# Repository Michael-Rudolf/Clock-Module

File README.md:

# Clock Module

This is the completely untested clock module for my (now) MRISC-CPU.
Don't use this shit.

## More info
Check README.pdf

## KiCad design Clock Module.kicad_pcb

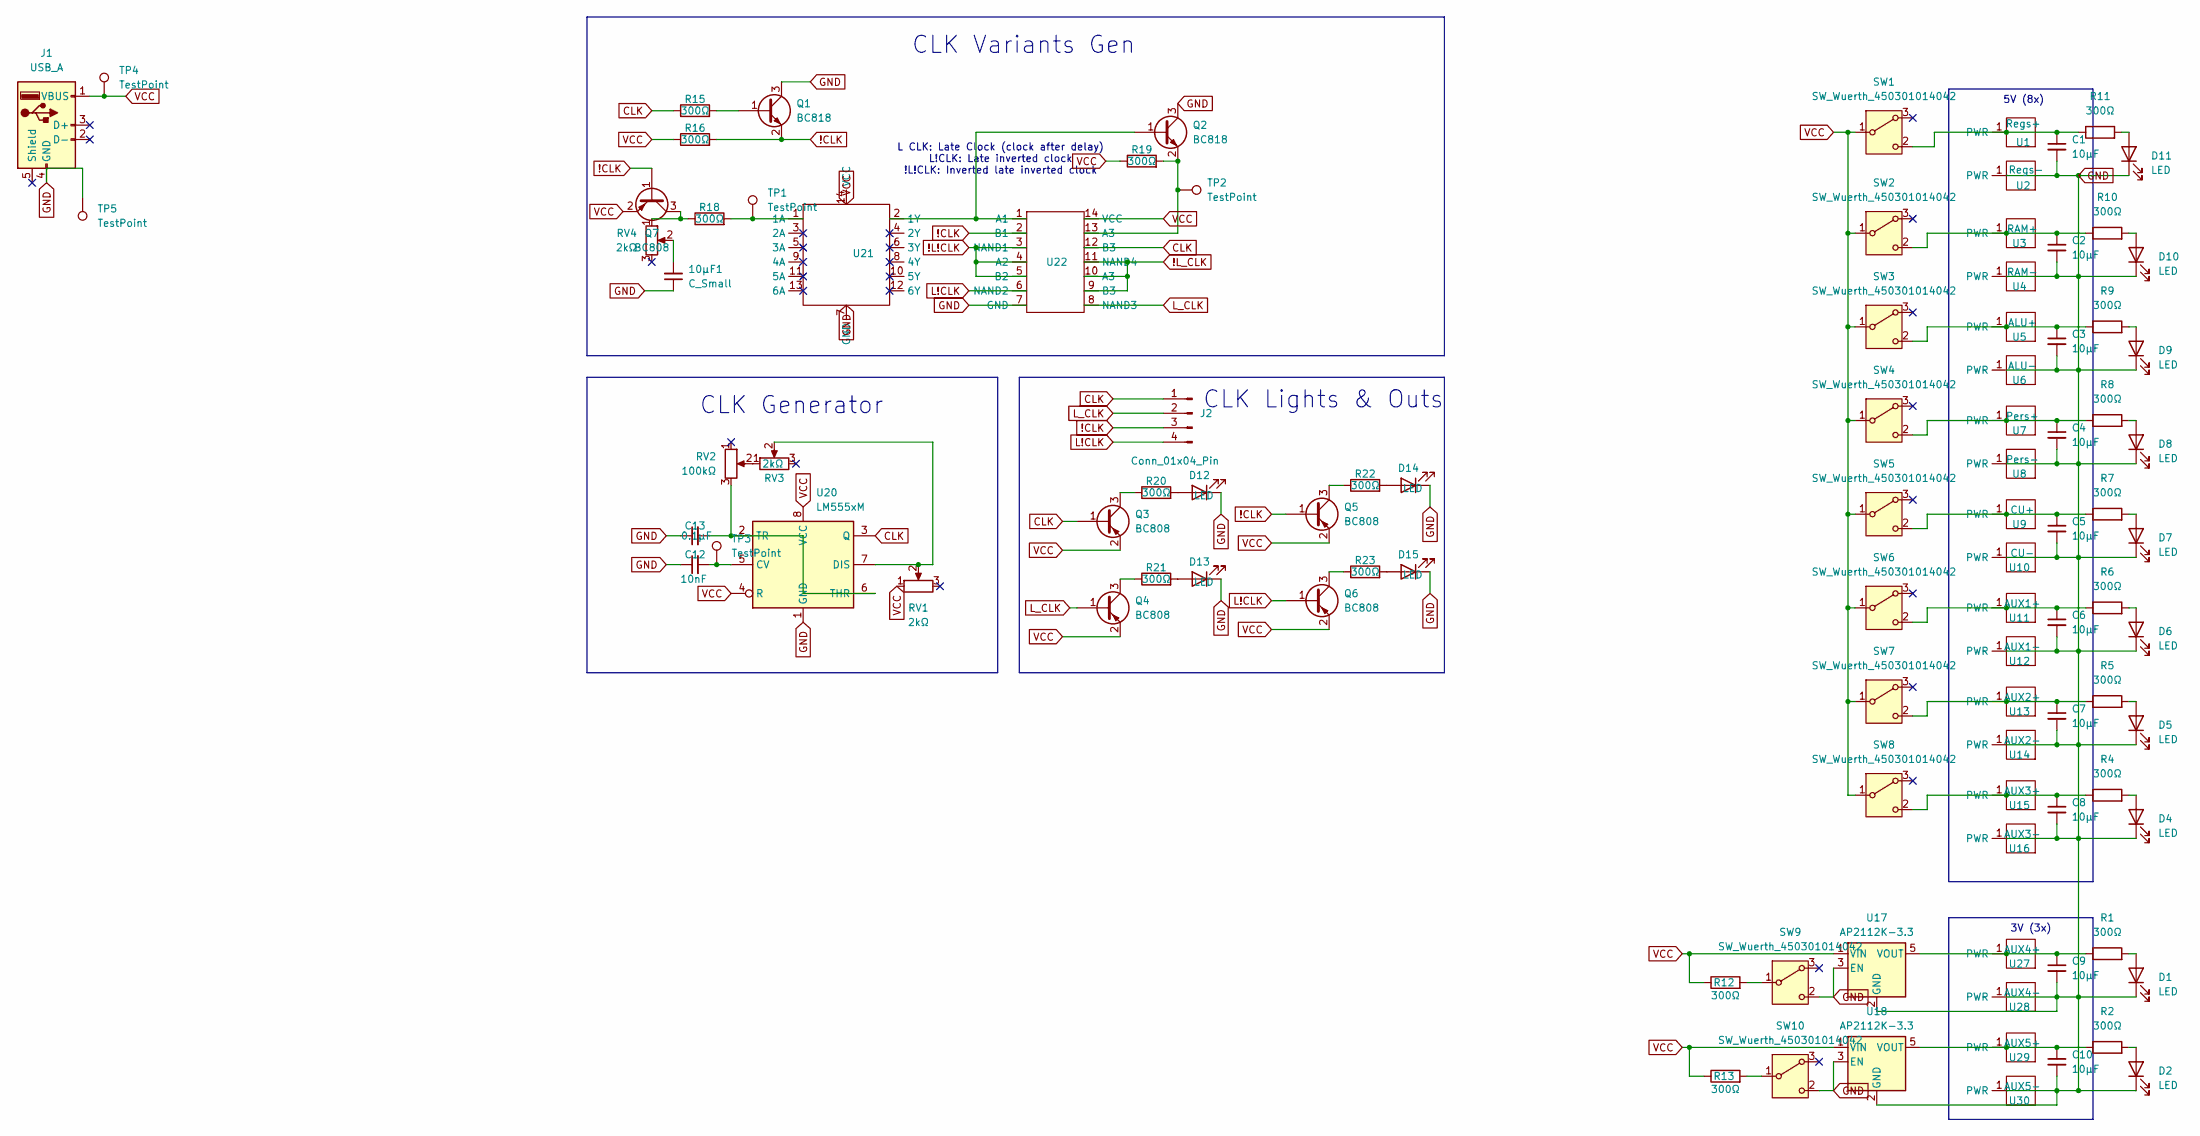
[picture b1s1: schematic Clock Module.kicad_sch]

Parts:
10µF1: C_Small; C_0805_2012Metric_Pad1.18x1.45mm_HandSolder
C1, C2, C3, C4, C5, C6, C7, C8, C9, C10: 10µF; C_0805_2012Metric
C12: 10nF; C_0805_2012Metric_Pad1.18x1.45mm_HandSolder
C13: 0.1µF; C_0805_2012Metric_Pad1.18x1.45mm_HandSolder
D1, D2, D4, D5, D6, D7, D8, D9, D10, D11, D12, D13, D14, D15: LED; LED_0805_2012Metric_Pad1.15x1.40mm_HandSolder
J1: USB_A; USB_A_CONNFLY_DS1095-WNR0
J2: Conn_01x04_Pin; PinHeader_1x04_P2.54mm_Vertical
Q1, Q2: BC818; SOT-23-3
Q3, Q4, Q5, Q6: BC808; SOT-23-3
Q7: BC808; SOT-23
R1, R2, R4, R5, R6, R7, R8, R9, R10, R11, R12, R13, R15, R16, R18, R19, R20, R21, R22, R23: 300Ω; R_0805_2012Metric_Pad1.20x1.40mm_HandSolder
RV1, RV3, RV4: 2kΩ; Potentiometer_Bourns_3299X_Horizontal
RV2: 100kΩ; Potentiometer_Bourns_3299X_Horizontal
SW1, SW2, SW3, SW4, SW5, SW6, SW7, SW8, SW9, SW10: SW_Wuerth_450301014042; SW_Slide-03_Wuerth-WS-SLTV_10x2.5x6.4_P2.54mm
TP1, TP2, TP3, TP4, TP5: TestPoint; TestPoint_Pad_1.0x1.0mm
U1: Regs+; Single Bit Mini Bus
U2: Regs-; Single Bit Mini Bus
U3: RAM+; Single Bit Mini Bus
U4: RAM-; Single Bit Mini Bus
U5: ALU+; Single Bit Mini Bus
U6: ALU-; Single Bit Mini Bus
U7: Pers+; Single Bit Mini Bus
U8: Pers-; Single Bit Mini Bus
U9: CU+; Single Bit Mini Bus
U10: CU-; Single Bit Mini Bus
U11: AUX1+; Single Bit Mini Bus
U12: AUX1-; Single Bit Mini Bus
U13: AUX2+; Single Bit Mini Bus
U14: AUX2-; Single Bit Mini Bus
U15: AUX3+; Single Bit Mini Bus
U16: AUX3-; Single Bit Mini Bus
U17, U18: AP2112K-3.3; SOT-23-5
U20: LM555xM; SOIC-8_3.9x4.9mm_P1.27mm
U21: TSSOP-14_4.4x5mm_P0.65mm
U22: SN74HC03
U27: AUX4+; Single Bit Mini Bus
U28: AUX4-; Single Bit Mini Bus
U29: AUX5+; Single Bit Mini Bus
U30: AUX5-; Single Bit Mini Bus

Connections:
!CLK: J2.3, Q1.2 (E), Q5.1 (B), Q7.1 (B), R16.2, U22.2 (B1)
!L!CLK: U22.3 (NAND1), U22.4 (A2), U22.5 (B2)
!L_CLK: U22.9 (B3), U22.10 (A3), U22.11 (NAND4)
CLK: J2.1, Q3.1 (B), R15.1, U20.3 (Q), U22.12 (B3)
GND: 10µF1.1, C1.2, C2.2, C3.2, C4.2, C5.2, C6.2, C7.2, C8.2, C9.2, C10.2, C12.1, C13.1, D1.1 (K), D2.1 (K), D4.1 (K), D5.1 (K), D6.1 (K), D7.1 (K), D8.1 (K), D9.1 (K), D10.1 (K), D11.1 (K), D12.1 (K), D13.1 (K), D14.1 (K), D15.1 (K), J1.4 (GND), Q1.3 (C), Q2.3 (C), SW9.2 (C), SW10.2 (C), TP5.1, U2.1 (PWR), U4.1 (PWR), U6.1 (PWR), U8.1 (PWR), U10.1 (PWR), U12.1 (PWR), U14.1 (PWR), U16.1 (PWR), U17.2 (GND), U17.3 (EN), U18.2 (GND), U18.3 (EN), U20.1 (GND), U21.7 (GND), U22.7 (GND), U28.1 (PWR), U30.1 (PWR)
L!CLK: J2.4, Q6.1 (B), U22.6 (NAND2)
L_CLK: J2.2, Q4.1 (B), U22.8 (NAND3)
unnamed: 10µF1.2, RV4.2
unnamed: D1.2 (A), R1.2
unnamed: D2.2 (A), R2.2
unnamed: D4.2 (A), R4.2
unnamed: D5.2 (A), R5.2
unnamed: D6.2 (A), R6.2
unnamed: D7.2 (A), R7.2
unnamed: D8.2 (A), R8.2
unnamed: D9.2 (A), R9.2
unnamed: D10.2 (A), R10.2
unnamed: D11.2 (A), R11.2
unnamed: D12.2 (A), R20.2
unnamed: D13.2 (A), R21.2
unnamed: D14.2 (A), R22.2
unnamed: D15.2 (A), R23.2
unnamed: Q1.1 (B), R15.2
unnamed: Q2.1 (B), U21.2 (1Y), U22.1 (A1)
unnamed: Q2.2 (E), R19.2, TP2.1, U22.13 (A3)
unnamed: Q3.3 (C), R20.1
unnamed: Q4.3 (C), R21.1
unnamed: Q5.3 (C), R22.1
unnamed: Q6.3 (C), R23.1
unnamed: Q7.3 (C), R18.1, RV4.1
unnamed: RV2.2, RV3.1
unnamed: C1.1, R11.1, SW1.2 (C), U1.1 (PWR)
unnamed: C2.1, R10.1, SW2.2 (C), U3.1 (PWR)
unnamed: C3.1, R9.1, SW3.2 (C), U5.1 (PWR)
unnamed: C4.1, R8.1, SW4.2 (C), U7.1 (PWR)
unnamed: C5.1, R7.1, SW5.2 (C), U9.1 (PWR)
unnamed: C6.1, R6.1, SW6.2 (C), U11.1 (PWR)
unnamed: C7.1, R5.1, SW7.2 (C), U13.1 (PWR)
unnamed: C8.1, R4.1, SW8.2 (C), U15.1 (PWR)
unnamed: R12.2, SW9.1 (B)
unnamed: R13.2, SW10.1 (B)
unnamed: C9.1, R1.1, U17.5 (VOUT), U27.1 (PWR)
unnamed: C10.1, R2.1, U18.5 (VOUT), U29.1 (PWR)
unnamed: C12.2, TP3.1, U20.5 (CV)
unnamed: RV1.2, RV3.2, U20.7 (DIS)
unnamed: C13.2, RV2.3, U20.2 (TR), U20.6 (THR)
unnamed: R18.2, TP1.1, U21.1 (1A)
VCC: J1.1 (VBUS), Q3.2 (E), Q4.2 (E), Q5.2 (E), Q6.2 (E), Q7.2 (E), R12.1, R13.1, R16.1, R19.1, RV1.1, SW1.1 (B), SW2.1 (B), SW3.1 (B), SW4.1 (B), SW5.1 (B), SW6.1 (B), SW7.1 (B), SW8.1 (B), TP4.1, U17.1 (VIN), U18.1 (VIN), U20.4 (R), U20.8 (VCC), U21.14 (VCC), U22.14 (VCC)

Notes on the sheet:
CLK Generator
CLK Variants Gen
CLK Lights & Outs
L CLK: Late Clock (clock after delay) L!CLK: Late inverted clock !L!CLK: Inverted late inverted clock
3V (3x)
5V (8x)

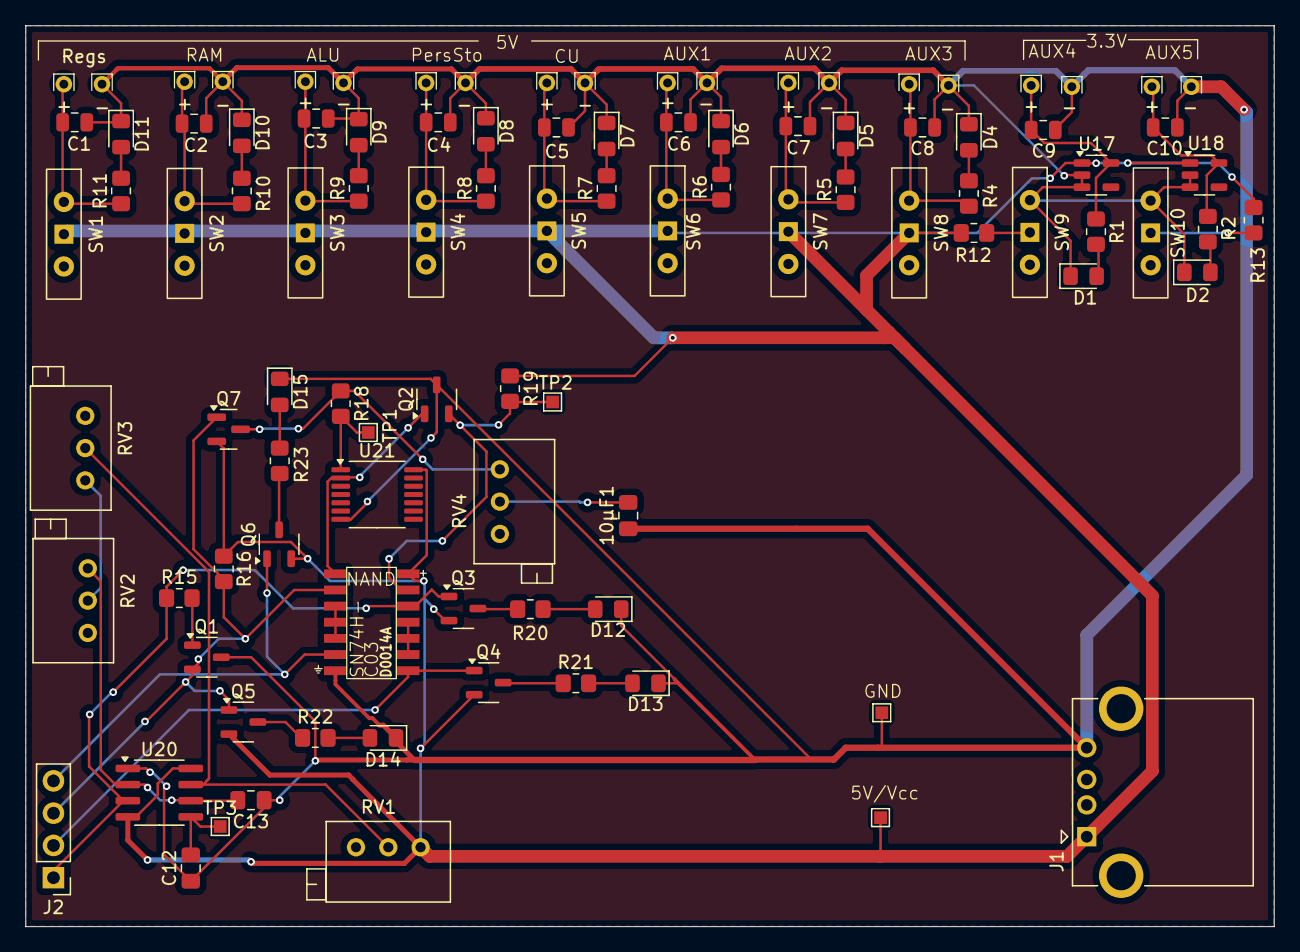
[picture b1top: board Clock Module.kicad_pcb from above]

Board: 2 copper layers, 98.2 x 70.9 mm, 100 parts (0 on the bottom side), 48 nets.

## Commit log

2025-07-09 Added information PDF
